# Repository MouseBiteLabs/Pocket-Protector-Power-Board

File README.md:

# Pocket Protector Power Board

This is a power regulator board for my <a href="https://github.com/MouseBiteLabs/Game-Boy-Pocket-Color">Game Boy Pocket Color (MGBC)</a> project for use with LiPo batteries. But hey, have you seen my other regulator board, the <a href="https://github.com/MouseBiteLabs/Pocket-Mouse-Power-Board">Pocket Mouser Power Board</a>? It's also really cool and doesn't use a battery that can explode.

## Important Things Before You Start

I highly suggest testing this board before installation in a Game Boy. Failure to do so may result in an irreversibly damaged Game Boy. See the testing sequence below.

**This is a complicated build that requires high level soldering skills. Please do not attempt if you do not have advanced soldering experience. Do not attempt to hand-solder the QFN components on this board, you must use a hot plate.**

**I am not responsible for any damage done to you, your Game Boy, or your dwelling. Lithium ion batteries are a huge fire hazard. You accept any and all risks associated with attempting this project.**

## Mandatory Reading About Battery Safety

"Bucket Mouse, all my devices have lithium ion batteries in them, and they're not dangerous. Why are you fear mongering?"

I am but one hobbyist, making things in my room. The batteries and battery management systems you use in devices every day are created by engineering teams and produced by corporations who do rigorous testing on products they sell (or, at least, they are supposed to). 

Therefore, for projects you assemble yourself, it is 100% up to *you* to safely manage these batteries, and know what you are doing, and know what to look out for with the batteries you purchase. This circuit board works for me, but as I am only one person, I have blind spots and I may have missed something (please tell me if I have). Also, I am confident in my soldering abilities - I am inherently *not* confident in yours. So, please, understand these risks and proceed at your own peril.

Read this article before continuing down this path: https://batteryuniversity.com/article/lithium-ion-safety-concerns

## Board Characteristics and Order Information

### Power Board

This is the board that sits in the U5 socket on the MGBC board.

The zipped folder contains all the gerber files for this board.
-	Layers: 4
-	Thickness: 1.6mm or thinner
-	Surface Finish: ENIG is recommended, HASL will work too

You can use the zipped folder with the gerber files at any board fabricator you like. **I am not selling this board.**

Hosted on OSH Park here: https://oshpark.com/shared_projects/uPHw8orH

### USB-C Adapter Board

This breakout board adapts a USB-C port to the MGBC's DC jack footprint. Assemble the parts to this board (may need to trim the USB-C port legs to be flush with the board), then place on the MGBC board and flow solder into the DC jack socket holes through to the pads on the back of this board to secure it.

The zipped folder contains all the gerber files for this board.
-	Layers: 2
-	Thickness: 1.2mm is recommended
-	Surface Finish: HASL or ENIG

You can use the zipped folder with the gerber files at any board fabricator you like. **I am not selling this board.**

Hosted on OSH Park here: https://oshpark.com/shared_projects/hsA91SMe

## Features

Some features of this power board include: 

* Changing the power switch to a "soft power switch," meaning the main power of the Game Boy does not flow through the switch. A dirty power switch can severly impact performance, so using this scheme can remedy that issue.
* Bootloop protection circuitry to prevent overdischarge of the battery past 3 V (a safe limit for lithium ion batteries), and to allow the Game Boy to die gracefully instead of violently stuttering until the regulator gives up.
* Load sharing (aka "power path") for charge-and-play capability.

This board was tested exclusively with this battery; any deviation from this one is 100% up to the user to determine compatibility: https://retrogamerepairshop.com/collections/gbp-power/products/102045-900mah-lipo-battery-cell?variant=40148887437484

**This battery includes a DW01 protection IC to prevent overcharge and deep overdischarge. Any battery used in this build must include a DW01 protection IC. This circuit board does not include these protections.**

## Alternate LiPo Options

If you are at all doubting your ability to assemble this board, I recommend Nataliethenerd's Safer Charge DC, as it comes pre-assembled with everything you need: https://www.nataliethenerd.com/product-page/safer-charge-dc

Another option is to **have someone more skilled than you assemble the board for you.** I am not one of those people, but they certainly exist.

## Successful Build Requirements

In order to effectively, properly, and *safely* build this board, you really must:

1) Read this *entire* README thoroughly and carefully
2) Use a lithium ion battery that has an internal DW01 protection IC - **NO BARE CELLS**
3) Use a hot plate and solder paste for good part placement
4) Own a multimeter for testing voltages and measuring resistance/continuity
5) Have advanced soldering skills
6) Have modded a Game Boy console before
7) Have a lot of patience (do not rush!)
8) Double check the assembled board before final installment using the testing procedure below
9) Have homeowner's/renter's insurance

## Testing and Installation Steps

Testing the assembled board *is mandatory.* If you have misassembled it, a part is incorrect, if there is a hidden solder bridge, or one of many other issues - your 5 V supply might be too high when you turn it on! This is not ideal for your Game Boy! But also, importantly, you may cause damage to your battery (which can explode). So you absolutely need to make sure everything is connected properly and working as expected.

### Equipment

1) You will need a multimeter to check resistances and voltages.
2) You should have some sort of power source, like a AA battery holder with alligator clips or benchtop power supply. *You can use the lithium ion battery to test for all steps, but I would recommend something a bit safer for the initial 5V supply test if possible.*
3) I highly recommend getting test leads with clips, like this: https://mou.sr/47Yeuae. They really make testing easier without having to solder wires on.

### Step 1: Top Side Assembly and Testing for Short Circuits

Assemble the top side parts using a hot plate and solder paste. **Do not assemble the bottom side yet, as this will make reworks on the top side much more painful to perform if you find errors later.** 

Afterwards, you'll want to check for short circuits on the charging IC (U3) with a multimeter. Finding them now will make your life much easier later. A short circuit will read as approximately 0 ohms on your multimeter. You can access (nearly) all the pertinent points via the backside of the PCB. See net definitions here:

Check to make sure the following measurements are **not** short circuited (0 ohms):

1) BT+ and VUSB
2) BT+ and GND
3) VUSB and R7
4) VUSB and GND
5) VUSB and VPOS
6) R9 and GND
7) R9 and VPOS
8) VPOS and SW
9) VPOS and VCC
10) VPOS and 5V
11) VPOS and DC

One last measurement is the resistance across the terminals of R10 (on the front of the board). It should read approximately 2.49 kΩ, +/- 1%.

Any measured short circuits indicates a solder bridge somewhere on the board, most likely on the QFN package.

### Step 2: Testing 5V Supply

The next step that will make your life easier later is to test the 5V generation handled by the *other* QFN device, U1.

1) Populate R5 on the backside of the board.
2) Connect pin 3 of the board to the negative end of a power source (like a battery holder or benchtop power supply).
3) Connect pin 2 (VCC) to the positive side of the power source.
4) Connect pin 1 (SW) to the positive side of the power source *after* pin 2 is connected. Turn the switch on (if you have a switch).
5) Measure the 5V output - positive multimeter probe on pin 7 of the board, negative probe on GND.

If your voltage measures anything but 5V (+/-1%) then you have an issue. Probably a solder bridge underneath U1. Get to troubleshooting!

### Step 3: Populate the Back of the Board and Check Resistances

The bottom side of the board is easy to hand solder - this was done on purpose! ;)

Then check these resistances with a multimeter:

1) Check R9. It must be approximately 10 kΩ.
2) Check R10 (on the front of the board). It must (still) be approximately 2.49 kΩ.

This will also tell you if you have any new short circuits after assembling more parts. If you measure anything else, outside of a 1% margin, then something is wrong and it may be *dangerous* to use the board. Find the problem!

### Step 4: Preparing and Installing the USB-C Board

**The following steps requires the main MGBC board. The rest of this procedure assumes the MGBC is properly built.**

The USB-C breakout board sits on top of where the DC jack used to be. The board thickness should be 1.2mm for best fitment. 

1) Trim the legs of the USB-C port before soldering it in the board, so that the bottom of the board is a flush surface.
2) Solder in the port, then the 5.1kΩ resistors R1 and R2.
3) Place the board on top of the MGBC board, line up the solder pads through the holes, and flow solder through all five holes to secure it to the board.

### Step 5: Charge Testing

*Note: Charging will not work if F2 is blown. If you hare having issues, don't forget to check F2 for continuity.*

To set up the system for charging:

1) Connect the battery to the LIPO + and - holes on the power board using clips or wires. The DW01 should protect you if you short circuit the + and - wires together while you're soldering them in, but try to avoid it anyway.
2) Connect pins 1, 2, and 3 of the power board socket to the power board using clips or wires - don't mount it to the MGBC just yet.
3) Connect the DC hole on the power board to the DC hole on the MGBC.
4) If your MGBC board revision is v1.6 or earlier, make sure you have removed EM7 on the MGBC board. If you have v2.0 or later, **do not** remove EM7.

Measure the voltage of the battery with your multimeter. This should be measured from LIPO + pin to GND. Note what the voltage is - if it's higher than 4.1 V, then your battery is already fully charged so you may not be able to actually test the charging yet.

Now, plug in a USB-C cable to charge the battery. The red LED should come on. Once the red LED turns off by itself, the charge cycle is complete, and the voltage should measure around 4.1 V when fully charged. If the battery voltage ever rises *above* 4.2 V while charging, there may very well be a problem on your board assembly AND/OR the DW01 on your battery may be defective!

### Step 6: Testing 5V Supply With Lithium Ion Battery

*Note: The power will not turn on if F1 is blown. If you hare having issues, don't forget to check F1 for continuity.*

Disconnect the USB-C cable, and disconnect at least the positive lead of the battery. Make sure any residual charge on the 5V output is gone. Measure the voltage (positive probe on pin 7, negative probe on GND) and make sure it's 0 V (or close to it). Then, perform the following steps:

1) Connect the BT+ hole on the MGBC to the BT+ hole on the power board. **Be sure the 5V wire is still not connected (pin 7).**
2) Reconnect the battery as before.

Now, check the voltage on pin 2 of the power board (VCC): positive probe on pin 2, negative probe on GND. It should read somewhere between 3 V and 4.2 V (it will be your battery voltage). If you read 0 V, plug in your USB-C cable again and check to make sure the red LED turns on. Then measure the voltage to make sure the battery voltage appears on VCC. (If your DW01 tripped due to an overcurrent, like if you accidentally shorted the positive lead to GND, charging the battery will clear the error).

Now you should be able to turn on the 5V supply with the power switch on the MGBC. Test with the multimeter to make sure the 5V is output when the switch is on. Note that when the switch is off, the output capacitors will still hold a charge on the 5V output, so you will likely read a slowly discharging voltage when the switch is off. The important thing is to make sure the voltage output is a solid 5V (plus or minus 1% margin).

### Step 7: Final Testing and Assembly

As long as your 5 V output is the proper voltage, you can now finally connect the 5 V output to the MGBC board. **Make sure the power switch is off when you do this.** Check to make sure everything works as expected, and you can remove all the clips and test leads and permanently solder the board in (it is probably best to remove the battery while you do this, and add it in last). 

You may have to put the battery inside the back shell and *then* solder the wires into the power board. If you end up having any exposed metal, like if you spliced wires together, make sure you insulate the exposed area so you don't have any accidental short circuits.

## Bill of Materials

A prepopulated cart from Mouser can be found here: https://www.mouser.com/ProjectManager/ProjectDetail.aspx?AccessID=26118b92c3. You may want to consider ordering multiple quantities of some parts just in case you lose some during assembly.

### Regulator Board

| Reference Designators       | Qty | Value/Part Number  | Package  | Description      | Source                                           |
| --------------------------- | --- | ------------------ | -------- | ---------------- | ------------------------------------------------ |
| C1, C3, C5                  | 3   | 22uF               | 0805     | Capacitor (MLCC) | [https://mou.sr/46mVnVR](https://mou.sr/46mVnVR) |
| C2, C6                      | 2   | 10uF               | 0603     | Capacitor (MLCC) | [https://mou.sr/3mZtSkF](https://mou.sr/3mZtSkF) |
| C4                          | 1   | 0.1uF              | 0603     | Capacitor (MLCC) | [https://mou.sr/3ENc15O](https://mou.sr/3ENc15O) |
| D1                          | 1   | SMF5.0A-T13        | SOD-123  | TVS Diode        | [https://mou.sr/46lYsWi](https://mou.sr/46lYsWi) |
| D2                          | 1   | 150060RS75000      | 0603     | LED              | [https://mou.sr/3ul6dOR](https://mou.sr/3ul6dOR) |
| D3                          | 1   | VSS8D5M12HM3/H     | DO-221AD | Schottky Diode   | [https://mou.sr/3sHvulW](https://mou.sr/3sHvulW) |
| L1                          | 1   | 2.2uH              | 1212     | Inductor         | [https://mou.sr/49Sn9vE](https://mou.sr/49Sn9vE) |
| Q1                          | 1   | MMBT3906           | SOT23    | PNP BJT          | [https://mou.sr/3G7ub2I](https://mou.sr/3G7ub2I) |
| Q2, Q4                      | 2   | 2N7002             | SOT23    | N-channel MOSFET | [https://mou.sr/3rgfh6J](https://mou.sr/3rgfh6J) |
| Q3                          | 1   | MMBT3904           | SOT23    | NPN BJT          | [https://mou.sr/3Rv7yfA](https://mou.sr/3Rv7yfA) |
| R1, R4, R6, R8              | 4   | 100k               | 0603     | Resistor         | [https://mou.sr/49bgMnu](https://mou.sr/49bgMnu) |
| R2, R3, R5, R7, R9, R11     | 6   | 10k                | 0603     | Resistor         | [https://mou.sr/3riR7IH](https://mou.sr/3riR7IH) |
| R10                         | 1   | 2.49k              | 0603     | Resistor         | [https://mou.sr/3G7MS6w](https://mou.sr/3G7MS6w) |
| U1                          | 1   | TPS61202           | VSON-10  | Boost Converter  | [https://mou.sr/47hIE8c](https://mou.sr/47hIE8c) |
| U2                          | 1   | TPS3840DL30        | SOT23-5  | Supervisory IC   | [https://mou.sr/47JYTuN](https://mou.sr/47JYTuN) |
| U3                          | 1   | MCP73871-2CAI/ML   | QFN-20   |                  | [https://mou.sr/47F8yT5](https://mou.sr/47F8yT5) |
| \--                         | 1   | 10129378-904001BLF | \--      | 1x4 Header Pins  | [https://mou.sr/40SXaAX](https://mou.sr/40SXaAX) |
| \--                         | 1   | 10129378-903001BLF | \--      | 1x3 Header Pins  | [https://mou.sr/47nzLdm](https://mou.sr/47nzLdm) |

### USB-C Board

| Reference Designators | Qty | Value/Part Number | Package | Description     | Source                                           |
| --------------------- | --- | ----------------- | ------- | --------------- | ------------------------------------------------ |
| J1                    | 1   | 217175-0001       | 6 CKT   | USB-C Connector | [https://mou.sr/48BChgu](https://mou.sr/48BChgu) |
| R1, R2                | 2   | 5.1k              | 0603    | Resistor        | [https://mou.sr/49J9uru](https://mou.sr/49J9uru) |

### Battery

As explained before, the battery you use **must** include a DW01 protection device. **DO NOT USE BARE CELLS**. Also note that the battery you order might be defective itself, so it is **up to you** to make sure it's safe. If your battery ever feels warm, or you measure voltages less than 2.45 V or greater than 4.2 V, the battery is defective and *should **not** be used*.

Testing was done exclusively with this battery: https://retrogamerepairshop.com/collections/gbp-power/products/102045-900mah-lipo-battery-cell?variant=40148887437484

I cannot claim that this specific battery is guaranteed to be safe and undamaged upon arrival, as I am not the vendor, so I don't know where it is sourced from. It's just the one I used. I would recommend *against* buying really cheap batteries from places like AliExpress. See the article about battery safety I linked above, especially the section titled "What Every Battery User Should Know": https://batteryuniversity.com/article/lithium-ion-safety-concerns

## Potential Issues

- I really can't stress enough that this project needs to be done correctly. Lithium ion batteries are only as safe as you make them. I am also only one person; while I have tested this board a lot, there may be an inherent flaw I missed - this is another reason why it is mandatory to have a DW01 protection device on the battery. Another thing to keep in mind is that the battery you purchase has the chance to be defective as well! Safety while using this board is *paramount*.

## Revision History

### v1.3
- Removed a via
- Changed silkscreen information

### v1.2
- Changed silkscreen information
- Modified various component values and part placements

### v1.1
- Added a series diode to drop 5 V charging input down to a lower voltage, to prevent DCM in the regulator which caused audio interference
- Modified various component values and part placements

### v1.0
- Release version

## License
<br />This work is licensed under a <a rel="license" href="http://creativecommons.org/licenses/by-sa/4.0/">Creative Commons Attribution-ShareAlike 4.0 International License</a>. You are able to copy and redistribute the material in any medium or format, as well as remix, transform, or build upon the material for any purpose (even commercial) - but you **must** give appropriate credit, provide a link to the license, and indicate if any changes were made.

©MouseBiteLabs 2023

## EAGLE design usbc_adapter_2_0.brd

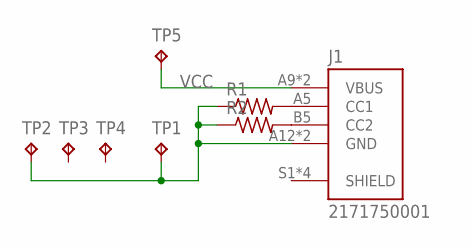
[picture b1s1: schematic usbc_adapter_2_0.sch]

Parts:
J1: 2171750001; MOLEX_2171750001
R1, R2: R-US_R0603; R0603
TP1, TP2, TP3, TP4: TPTP20R; TP20R
TP5: TPTP16R; TP16R

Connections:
GND: J1.A12 (GND), J1.B12 (GND), R1.1, R2.1, TP1.TP, TP2.TP
unnamed: J1.A5 (CC1), R1.2
unnamed: J1.B5 (CC2), R2.2
VCC: J1.A9 (VBUS), J1.B9 (VBUS), TP5.TP

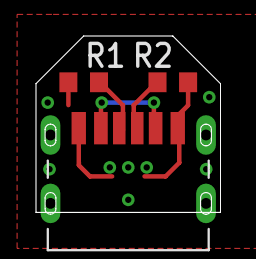
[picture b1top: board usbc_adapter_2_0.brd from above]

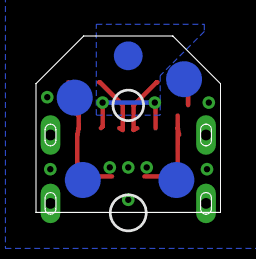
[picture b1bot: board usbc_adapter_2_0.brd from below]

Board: 2 copper layers, 10.2 x 9.8 mm, 8 parts (5 on the bottom side), 4 nets.

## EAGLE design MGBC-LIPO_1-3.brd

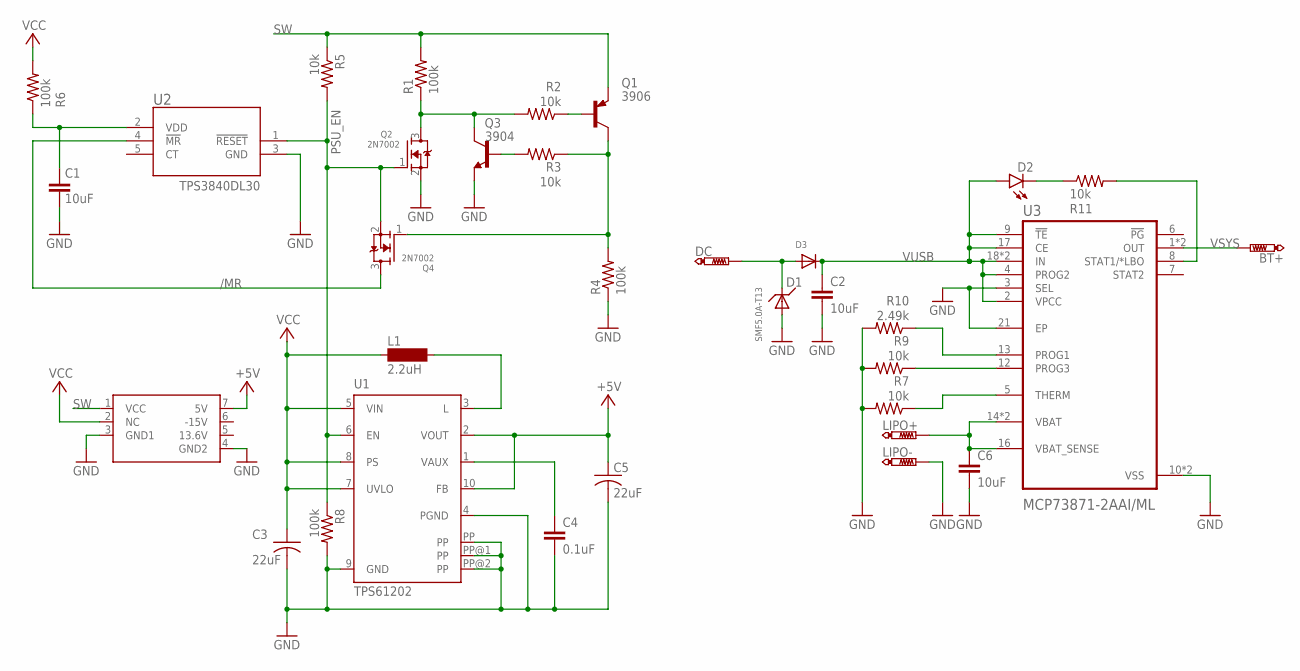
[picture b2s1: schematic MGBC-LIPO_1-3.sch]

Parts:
BT+: PTR1SLIM; P1-13S
C1: 10uF; C0805
C2, C6: 10uF; C0603
C3, C5: 22uF; C0805
C4: 0.1uF; C0603
D1: SMF5.0A-T13; SOD-123
D2: LEDSML0603; SML0603
D3: DIODESMA; SMADIODE
DC: PTR1SLIM; P1-13S
L1: 2.2uH; 1212
LIPO+: PTR1SLIM; P1-13S
LIPO-: PTR1SLIM; P1-13S
Q1: MMBT3906LT1SMD; SOT23-BEC
Q2, Q4: 2N7002; SOT23
Q3: 3904; SOT23-BEC
R1, R4, R6, R8: 100k; R0603
R2, R3, R5, R7, R9, R11: 10k; R0603
R10: 2.49k; R0603
U1: TPS61202; S-PDSO-N10
U2: TPS3840; SOT-23-5
U3: MCP73871-2AAI/ML; QFN50P400X400X100-21N
U$1: MGB-PWR_BD; MGB-PWRBD

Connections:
13.6V: U$1.5 (13.6V)
+5V: C5.1, U1.2 (VOUT), U1.10 (FB), U$1.7 (5V)
-15V: U$1.6 (-15V)
/MR: Q4.3 (D), U2.4 (!MR)
GND: C1.2, C2.2, C3.2, C4.2, C5.2, C6.2, D1.A, LIPO-.TP, Q2.2 (S), Q3.E, R4.1, R7.2, R8.2, R9.2, R10.2, U1.4 (PGND), U1.9 (GND), U1.PP, U1.PP@1 (PP), U1.PP@2 (PP), U2.3 (GND), U3.3 (SEL), U3.10 (VSS), U3.11 (VSS), U3.21 (EP), U$1.3 (GND1), U$1.4 (GND2)
L: L1.2, U1.3 (L)
unnamed: C1.1, R6.1, U2.2 (VDD)
unnamed: D1.C, D3.A, DC.TP
unnamed: R11.2, U3.8 (STAT1/*LBO)
unnamed: R7.1, U3.5 (THERM)
unnamed: R10.1, U3.13 (PROG1)
unnamed: R9.1, U3.12 (PROG3)
unnamed: D2.C, R11.1
unnamed: Q1.B, R2.1
unnamed: Q1.C, Q4.1 (G), R3.1, R4.2
unnamed: Q3.B, R3.2
unnamed: Q2.3 (D), Q3.C, R1.1, R2.2
unnamed: C4.1, U1.1 (VAUX)
PSU_EN: Q2.1 (G), Q4.2 (S), R5.2, R8.1, U1.6 (EN), U2.1 (!RESET)
SW: Q1.E, R1.2, R5.1, U$1.1 (VCC)
VCC: C3.1, L1.1, R6.2, U1.5 (VIN), U1.7 (UVLO), U1.8 (PS), U$1.2 (NC)
VSYS: BT+.TP, U3.1 (OUT), U3.20 (OUT)
VUSB: C2.1, D2.A, D3.C, U3.2 (VPCC), U3.4 (PROG2), U3.9 (!TE), U3.17 (CE), U3.18 (IN), U3.19 (IN)
V_POS: C6.1, LIPO+.TP, U3.14 (VBAT), U3.15 (VBAT), U3.16 (VBAT_SENSE)

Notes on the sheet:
3906
TPS3840DL30

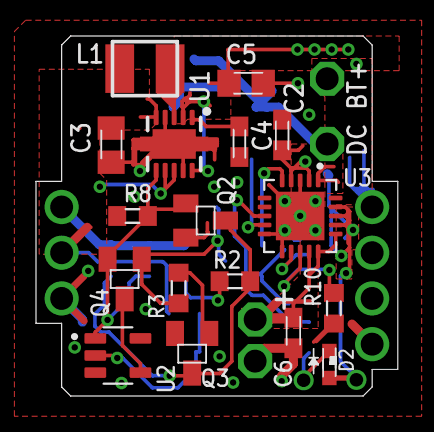
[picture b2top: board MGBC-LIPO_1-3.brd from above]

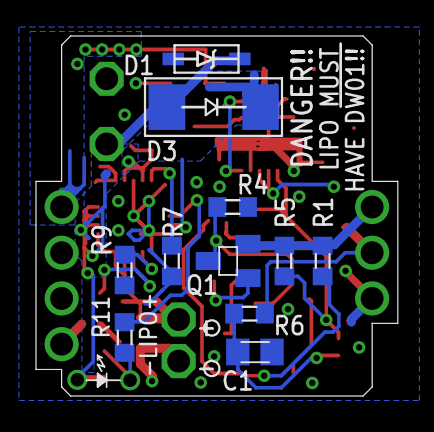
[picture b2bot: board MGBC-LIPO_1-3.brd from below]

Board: 4 copper layers, 20.1 x 20.0 mm, 33 parts (11 on the bottom side), 22 nets.

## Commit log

2024-04-14 Removed one of the short circuit tests
2024-08-17 Fixed OSH Links
